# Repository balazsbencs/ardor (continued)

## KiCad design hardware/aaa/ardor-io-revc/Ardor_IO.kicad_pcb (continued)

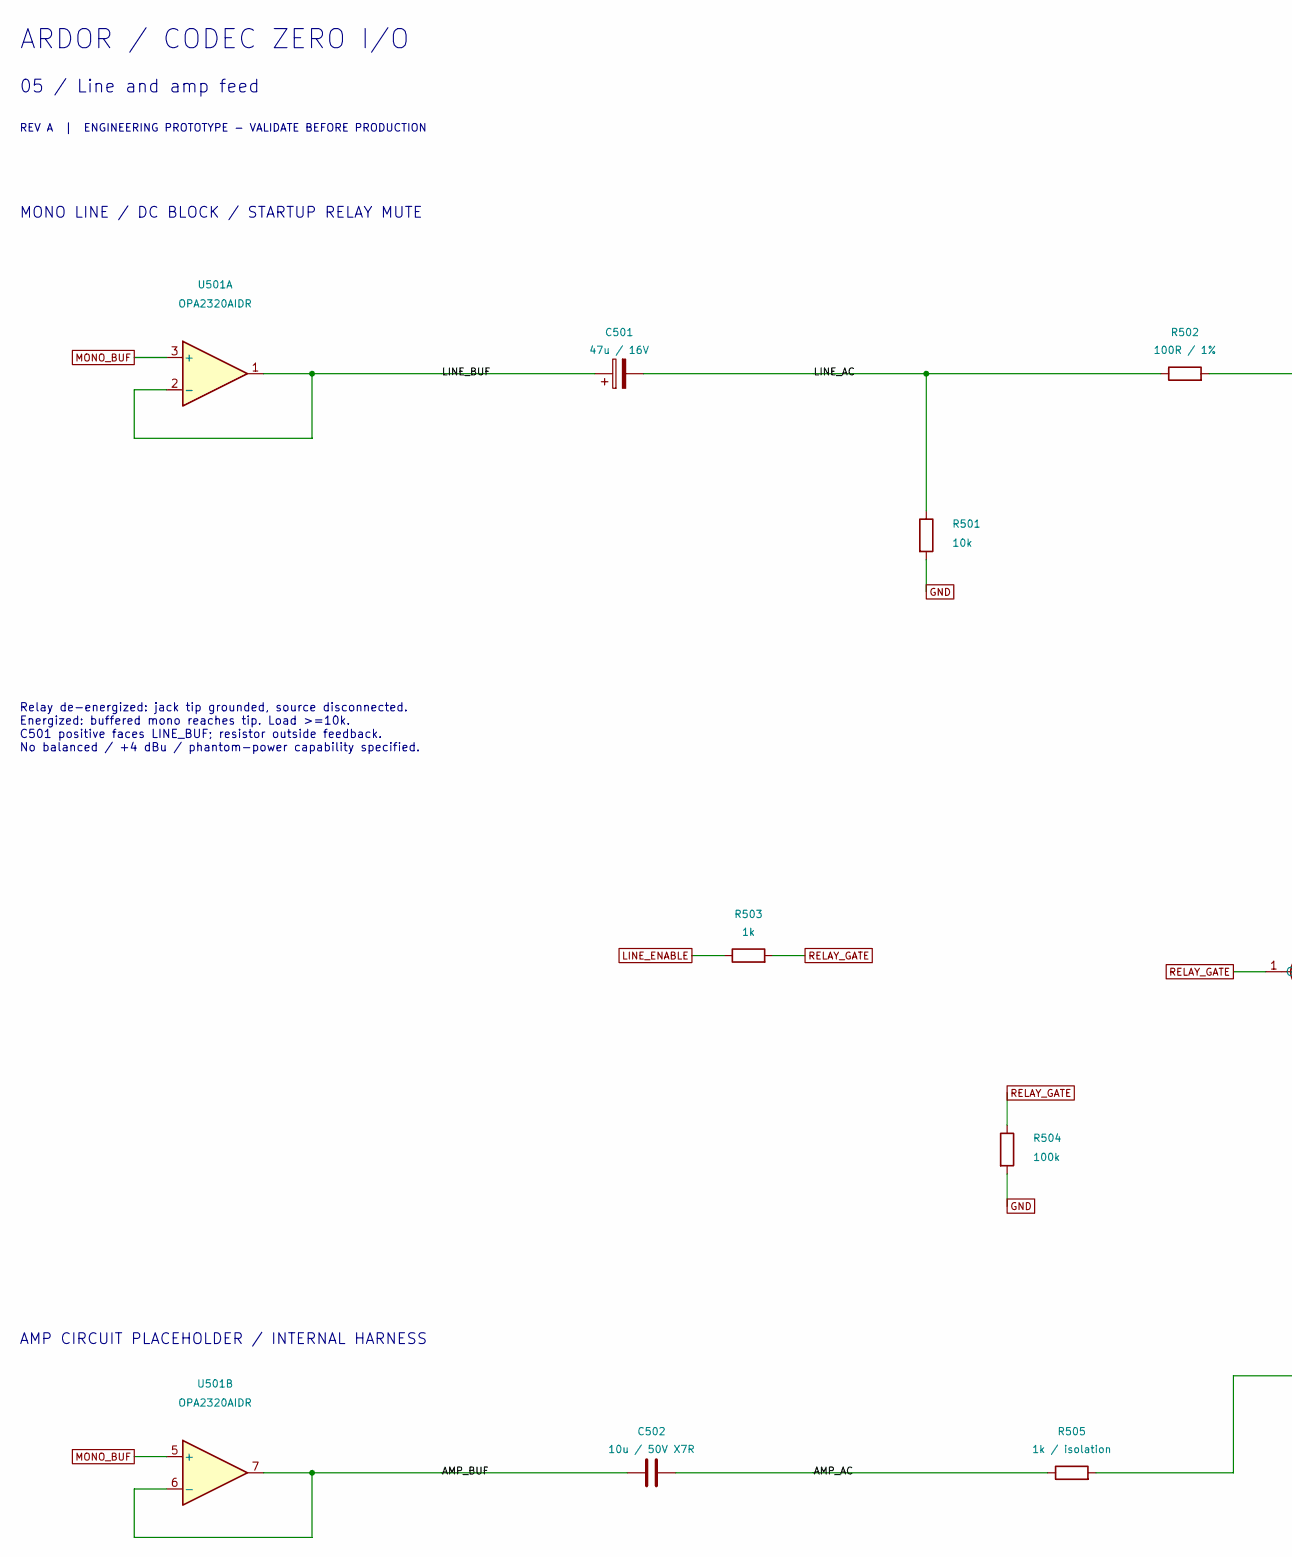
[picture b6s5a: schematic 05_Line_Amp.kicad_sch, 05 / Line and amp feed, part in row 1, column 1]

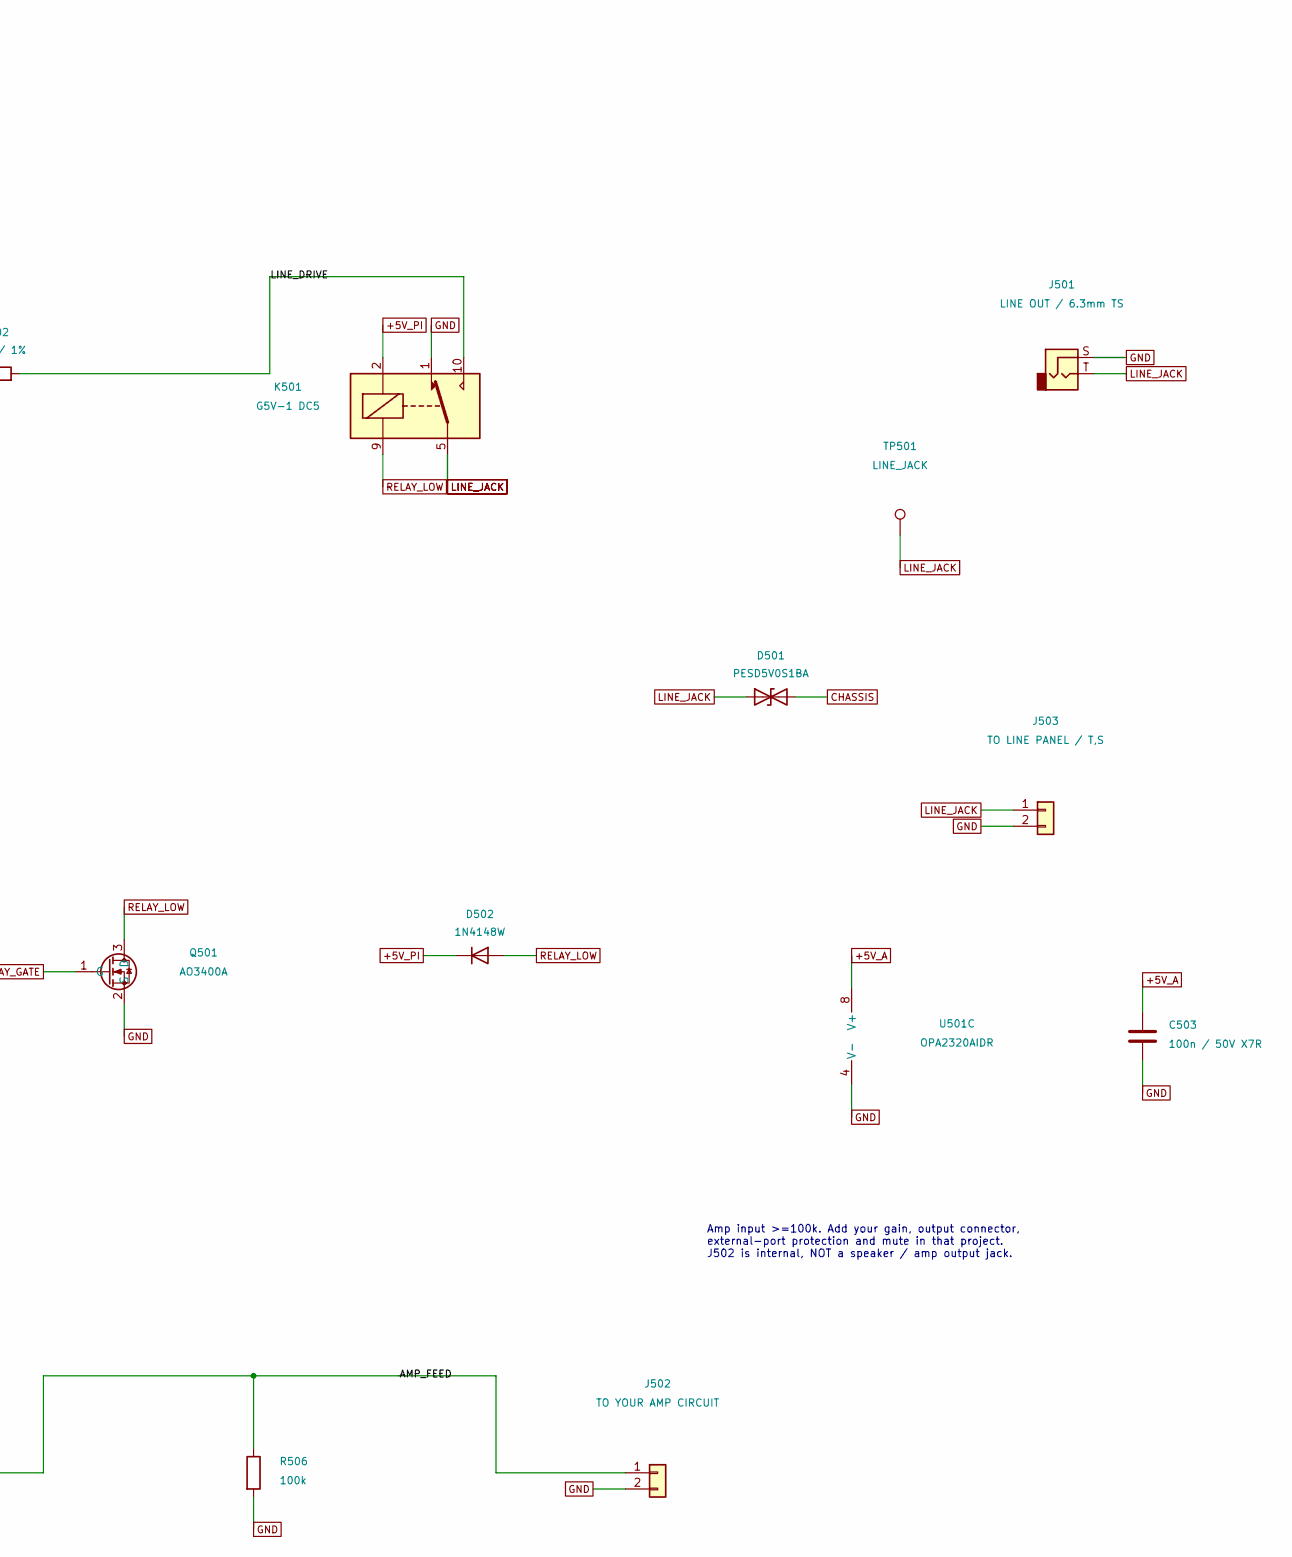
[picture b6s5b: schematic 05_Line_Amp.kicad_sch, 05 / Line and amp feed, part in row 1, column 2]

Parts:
C501: 47u / 16V; CP_Elec_Panasonic_FK_D6.3_H5.8; MPN Panasonic EEEFK1C470P; JLCPCB Part # C336261
C502: 10u / 50V X7R; C_1206_3216Metric; MPN Samsung CL31B106KBHNNNE; JLCPCB Part # C89632
C503: 100n / 50V X7R; C_0603_1608Metric; MPN YAGEO CC0603KRX7R9BB104; JLCPCB Part # C14663
D501: PESD5V0S1BA; D_SOD-323; MPN Nexperia PESD5V0S1BA,115; JLCPCB Part # C19224
D502: 1N4148W; D_SOD-123; MPN ST(Semtech) 1N4148W; JLCPCB Part # C81598
J501: LINE OUT / 6.3mm TS
J502: TO YOUR AMP CIRCUIT; PinHeader_1x02_P2.54mm_Vertical
J503: TO LINE PANEL / T,S; PinHeader_1x02_P2.54mm_Vertical
K501: G5V-1 DC5; Relay_SPDT_Omron_G5V-1; MPN Omron G5V-1 DC5
Q501: AO3400A; SOT-23; MPN Alpha & Omega AO3400A; JLCPCB Part # C20917
R501: 10k; R_0603_1608Metric; MPN UNI-ROYAL 0603WAF1002T5E; JLCPCB Part # C25804
R502: 100R / 1%; R_0603_1608Metric; MPN UNI-ROYAL 0603WAF1000T5E; JLCPCB Part # C22775
R503: 1k; R_0603_1608Metric; MPN UNI-ROYAL 0603WAF1001T5E; JLCPCB Part # C21190
R504, R506: 100k; R_0603_1608Metric; MPN UNI-ROYAL 0603WAF1003T5E; JLCPCB Part # C25803
R505: 1k / isolation; R_0603_1608Metric; MPN UNI-ROYAL 0603WAF1001T5E; JLCPCB Part # C21190
TP501: LINE_JACK; TestPoint_Pad_D1.5mm
U501: OPA2320AIDR; SOIC-8_3.9x4.9mm_P1.27mm; MPN TI OPA2320AIDR; JLCPCB Part # C2863402

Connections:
+5V_PI: D502.1 (K), K501.2; also elsewhere on the board
/05 / Line and amp feed/AMP_AC: C502.2, R505.1
/05 / Line and amp feed/AMP_FEED: J502.1, R505.2, R506.1
/05 / Line and amp feed/LINE_AC: C501.2, R501.1, R502.1
/05 / Line and amp feed/LINE_DRIVE: K501.10, R502.2
CHASSIS: D501.2 (A2); also elsewhere on the board
GND: C503.2, J501.S, J502.2, J503.2, K501.1, Q501.2 (S), R501.2, R504.2, R506.2, U501.4 (V-); also elsewhere on the board
LINE_ENABLE: R503.1; also elsewhere on the board
LINE_JACK: D501.1 (A1), J501.T, J503.1, K501.5, K501.6, TP501.1
unnamed: C503.1, U501.8 (V+)
unnamed: U501.3 (+), U501.5 (+)
RELAY_GATE: Q501.1 (G), R503.2, R504.1
RELAY_LOW: D502.2 (A), K501.9, Q501.3 (D)

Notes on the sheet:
ARDOR / CODEC ZERO I/O
05 / Line and amp feed
REV A | ENGINEERING PROTOTYPE - VALIDATE BEFORE PRODUCTION
MONO LINE / DC BLOCK / STARTUP RELAY MUTE
Relay de-energized: jack tip grounded, source disconnected. Energized: buffered mono reaches tip. Load >=10k. C501 positive faces LINE_BUF; resistor outside feedback. No balanced / +4 dBu / phantom-power capability specified.
AMP CIRCUIT PLACEHOLDER / INTERNAL HARNESS
Amp input >=100k. Add your gain, output connector, external-port protection and mute in that project. J502 is internal, NOT a speaker / amp output jack.

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
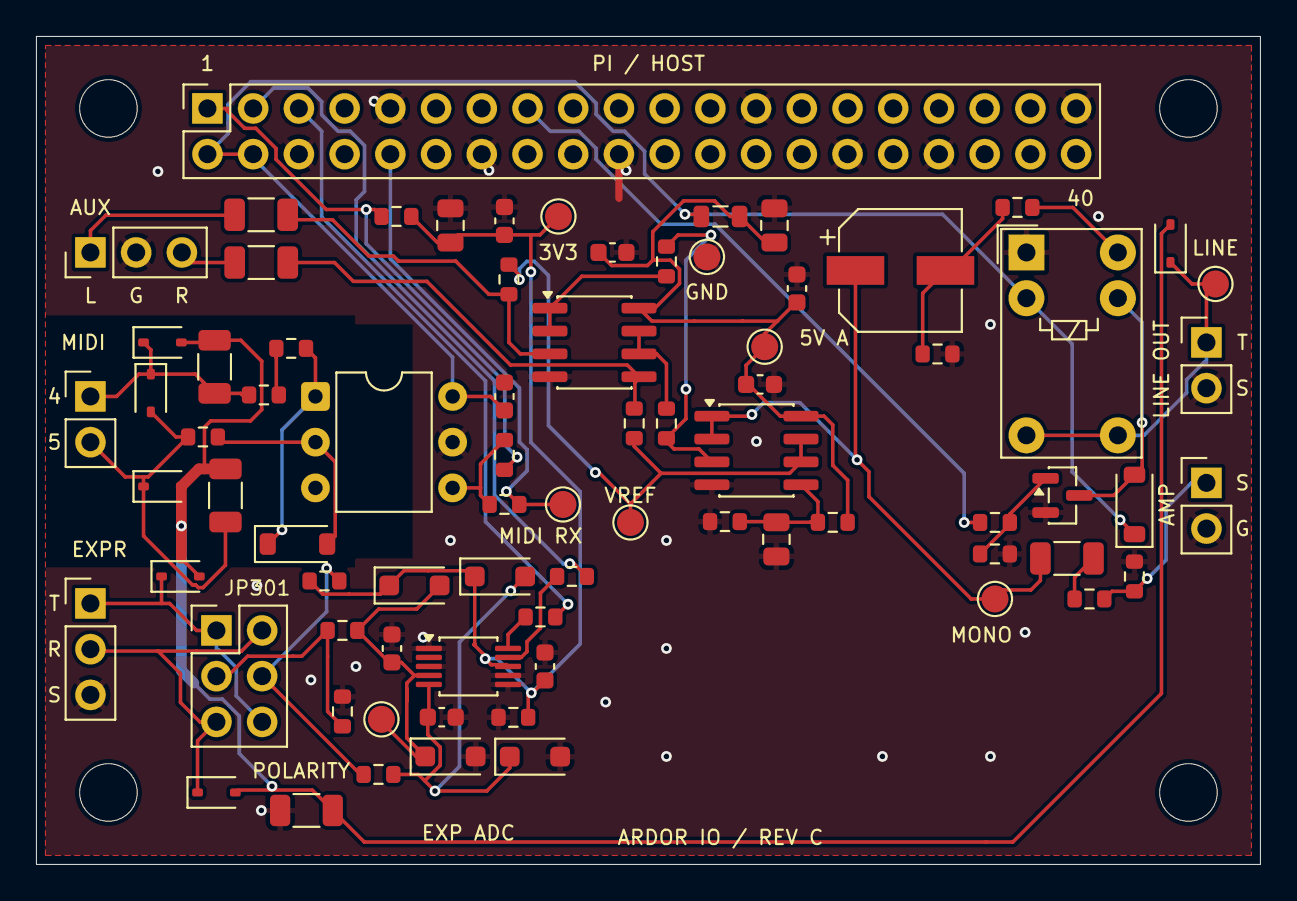
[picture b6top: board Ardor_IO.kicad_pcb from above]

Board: 2 copper layers, 68.0 x 46.0 mm, 81 parts (0 on the bottom side), 41 nets.

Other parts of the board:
H1, H2, H3, H4: M3 / PROVISIONAL; MountingHole_3.2mm_M3

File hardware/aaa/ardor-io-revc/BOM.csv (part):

Reference,Value,MPN,Footprint,Datasheet,Assembly,Sheet,JLCPCB Part #
J101,PI 40-PIN HEADER,Samtec SSQ-120-03-G-D (verify stack height),Connector_PinSocket_2.54mm:PinSocket_2x20_P2.54mm_Vertical,,PCB,1,
J102,CODEC AUX L / GND / R,,Connector_PinHeader_2.54mm:PinHeader_1x03_P2.54mm_Vertical,,PCB,1,
FB101,600R @100MHz,Murata BLM21PG601SN1D,Inductor_SMD:L_0805_2012Metric,https://www.murata.com/products/productdata/8796738977822/EN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,PCB,1,C41556732
C101,22u / 25V X5R,Samsung Electro-Mechanics CL21A226MAQNNNE,Capacitor_SMD:C_0805_2012Metric,https://www.lcsc.com/datasheet/lcsc_datasheet_2304140030_Sam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,PCB,1,C45783
C102,100n / 50V X7R,YAGEO CC0603KRX7R9BB104,Capacitor_SMD:C_0603_1608Metric,https://www.lcsc.com/datasheet/lcsc_datasheet_2211101700_YAG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,PCB,1,C14663
FB102,120R @100MHz,Murata Electronics BLM18PG121SN1D,Resistor_SMD:R_0603_1608Metric,https://www.lcsc.com/datasheet/lcsc_datasheet_2304140030_Mur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,PCB,1,C14709
C103,10u / 25V X5R,Samsung Electro-Mechanics CL21A106KAYNNNE,Capacitor_SMD:C_0805_2012Metric,https://www.lcsc.com/datasheet/lcsc_datasheet_2304140030_Sam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,PCB,1,C15850
C104,100n / 50V X7R,YAGEO CC0603KRX7R9BB104,Capacitor_SMD:C_0603_1608Metric,https://www.lcsc.com/datasheet/lcsc_datasheet_2211101700_YAG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,PCB,1,C14663
R101,0R / chassis bond,UNI-ROYAL 1206W4F0000T5E,Resistor_SMD:R_1206_3216Metric,https://www.lcsc.com/datasheet/lcsc_datasheet_2206010200_UNI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,PCB,1,C17888
J201,MIDI IN - PANEL DIN,,,,Panel / wired,2,
FB201,120R @100MHz,Murata Electronics BLM18PG121SN1D,Resistor_SMD:R_0603_1608Metric,https://www.lcsc.com/datasheet/lcsc_datasheet_2304140030_Mur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,PCB,2,C14709
R201,220R / 1%,UNI-ROYAL 0603WAF2200T5E,Resistor_SMD:R_0603_1608Metric,https://www.lcsc.com/datasheet/lcsc_datasheet_2206010130_UNI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,PCB,2,C22962
FB202,120R @100MHz,Murata Electronics BLM18PG121SN1D,Resistor_SMD:R_0603_1608Metric,https://www.lcsc.com/datasheet/lcsc_datasheet_2304140030_Mur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,PCB,2,C14709
D201,1N4148W,ST(Semtech) 1N4148W,Diode_SMD:D_SOD-123,https://www.lcsc.com/datasheet/lcsc_datasheet_1811061725_ST-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,PCB,2,C81598
U201,H11L1M,onsemi H11L1M,Package_DIP:DIP-6_W7.62mm,https://www.onsemi.com/pdf/datasheet/h11l3m-d.pdf,PCB,2,
C201,100n / 50V X7R,YAGEO CC0603KRX7R9BB104,Capacitor_SMD:C_0603_1608Metric,https://www.lcsc.com/datasheet/lcsc_datasheet_2211101700_YAG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,PCB,2,C14663
R202,1k / 1%,UNI-ROYAL 0603WAF1001T5E,Resistor_SMD:R_0603_1608Metric,https://www.lcsc.com/datasheet/lcsc_datasheet_2206010130_UNI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,PCB,2,C21190
R203,100R,UNI-ROYAL 0603WAF1000T5E,Resistor_SMD:R_0603_1608Metric,https://www.lcsc.com/datasheet/lcsc_datasheet_2411221126_UNI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,PCB,2,C22775
D202,PESD5V0S1BA,"Nexperia PESD5V0S1BA,115",Diode_SMD:D_SOD-323,https://assets.nexperia.com/documents/data-sheet/PESD5V0S1BA.pdf,PCB,2,C19224
C202,100p / 1kV C0G,CCTC TCC1206COG101J102DT,Capacitor_SMD:C_1206_3216Metric,https://wmsc.lcsc.com/wmsc/upload/file/pdf/v2/lcsc/230414003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,PCB,2,C367316
C203,100p / 1kV C0G,CCTC TCC1206COG101J102DT,Capacitor_SMD:C_1206_3216Metric,https://wmsc.lcsc.com/wmsc/upload/file/pdf/v2/lcsc/230414003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,PCB,2,C367316
D203,PESD24VL1BA,"Nexperia PESD24VL1BA,115",Diode_SMD:D_SOD-323,https://assets.nexperia.com/documents/data-sheet/PESD24VL1BA.pdf,PCB,2,C69324
D204,PESD24VL1BA,"Nexperia PESD24VL1BA,115",Diode_SMD:D_SOD-323,https://assets.nexperia.com/documents/data-sheet/PESD24VL1BA.pdf,PCB,2,C69324
J301,EXPRESSION / 6.3mm TRS,,,,Panel / wired,3,
JP301,POLARITY / 2 SHUNTS,,Connector_PinHeader_2.54mm:PinHeader_2x03_P2.54mm_Vertical,,PCB,3,
R301,1k / 1%,UNI-ROYAL 0603WAF1001T5E,Resistor_SMD:R_0603_1608Metric,https://www.lcsc.com/datasheet/lcsc_datasheet_2206010130_UNI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,PCB,3,C21190
R302,10k / 1%,UNI-ROYAL 0603WAF1002T5E,Resistor_SMD:R_0603_1608Metric,https://www.lcsc.com/datasheet/lcsc_datasheet_2206010045_UNI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,PCB,3,C25804
R303,1M,UNI-ROYAL 0603WAF1004T5E,Resistor_SMD:R_0603_1608Metric,https://www.lcsc.com/datasheet/lcsc_datasheet_2206010130_UNI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,PCB,3,C22935
C301,100n / 50V X7R,YAGEO CC0603KRX7R9BB104,Capacitor_SMD:C_0603_1608Metric,https://www.lcsc.com/datasheet/lcsc_datasheet_2211101700_YAG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,PCB,3,C14663
D303,BAT54H,"Nexperia BAT54H,115",Diode_SMD:D_SOD-123F,https://www.lcsc.com/datasheet/lcsc_datasheet_2407241029_Nex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,PCB,3,C426769
D304,BAT54H,"Nexperia BAT54H,115",Diode_SMD:D_SOD-123F,https://www.lcsc.com/datasheet/lcsc_datasheet_2407241029_Nex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,PCB,3,C426769
D301,PESD5V0S1BA,"Nexperia PESD5V0S1BA,115",Diode_SMD:D_SOD-323,https://assets.nexperia.com/documents/data-sheet/PESD5V0S1BA.pdf,PCB,3,C19224
D302,PESD5V0S1BA,"Nexperia PESD5V0S1BA,115",Diode_SMD:D_SOD-323,https://assets.nexperia.com/documents/data-sheet/PESD5V0S1BA.pdf,PCB,3,C19224
U301,ADS1115IDGS,TI ADS1115IDGSR,Package_SO:VSSOP-10_3x3mm_P0.5mm,https://www.ti.com/lit/ds/symlink/ads1115.pdf,PCB,3,C37593
R304,10k / 1%,UNI-ROYAL 0603WAF1002T5E,Resistor_SMD:R_0603_1608Metric,https://www.lcsc.com/datasheet/lcsc_datasheet_2206010045_UNI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,PCB,3,C25804
C302,100n / 50V X7R,YAGEO CC0603KRX7R9BB104,Capacitor_SMD:C_0603_1608Metric,https://www.lcsc.com/datasheet/lcsc_datasheet_2211101700_YAG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,PCB,3,C14663
C303,100n / 50V X7R,YAGEO CC0603KRX7R9BB104,Capacitor_SMD:C_0603_1608Metric,https://www.lcsc.com/datasheet/lcsc_datasheet_2211101700_YAG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,PCB,3,C14663
R305,33R,UNI-ROYAL 0603WAF330JT5E,Resistor_SMD:R_0603_1608Metric,https://www.lcsc.com/datasheet/lcsc_datasheet_2206010116_UNI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,PCB,3,C23140
R306,33R,UNI-ROYAL 0603WAF330JT5E,Resistor_SMD:R_0603_1608Metric,https://www.lcsc.com/datasheet/lcsc_datasheet_2206010116_UNI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,PCB,3,C23140
R307,2.2k / rail bleed,UNI-ROYAL 0603WAF2201T5E,Resistor_SMD:R_0603_1608Metric,https://www.lcsc.com/datasheet/lcsc_datasheet_2206010230_UNI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,PCB,3,C4190
D305,BAT54H,"Nexperia BAT54H,115",Diode_SMD:D_SOD-123F,https://www.lcsc.com/datasheet/lcsc_datasheet_2407241029_Nex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,PCB,3,C426769
D306,BAT54H,"Nexperia BAT54H,115",Diode_SMD:D_SOD-123F,https://www.lcsc.com/datasheet/lcsc_datasheet_2407241029_Nex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,PCB,3,C426769
C401,10u / 50V X5R,Samsung Electro-Mechanics CL31A106KBHNNNE,Capacitor_SMD:C_1206_3216Metric,https://www.lcsc.com/datasheet/lcsc_datasheet_2304140030_Sam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,PCB,4,C13585
R401,100k / 1%,UNI-ROYAL 0603WAF1003T5E,Resistor_SMD:R_0603_1608Metric,https://www.lcsc.com/datasheet/lcsc_datasheet_2206010045_UNI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,PCB,4,C25803
U401,TLV9002IDR,Texas Instruments TLV9002IDR,Package_SO:SOIC-8_3.9x4.9mm_P1.27mm,https://www.lcsc.com/datasheet/lcsc_datasheet_2304140030_Tex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,PCB,4,C398360
R403,10k / 1%,UNI-ROYAL 0603WAF1002T5E,Resistor_SMD:R_0603_1608Metric,https://www.lcsc.com/datasheet/lcsc_datasheet_2206010045_UNI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,PCB,4,C25804
C402,10u / 50V X5R,Samsung Electro-Mechanics CL31A106KBHNNNE,Capacitor_SMD:C_1206_3216Metric,https://www.lcsc.com/datasheet/lcsc_datasheet_2304140030_Sam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,PCB,4,C13585
R402,100k / 1%,UNI-ROYAL 0603WAF1003T5E,Resistor_SMD:R_0603_1608Metric,https://www.lcsc.com/datasheet/lcsc_datasheet_2206010045_UNI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,PCB,4,C25803
R404,10k / 1%,UNI-ROYAL 0603WAF1002T5E,Resistor_SMD:R_0603_1608Metric,https://www.lcsc.com/datasheet/lcsc_datasheet_2206010045_UNI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,PCB,4,C25804
U402,TLV9002IDR,Texas Instruments TLV9002IDR,Package_SO:SOIC-8_3.9x4.9mm_P1.27mm,https://www.lcsc.com/datasheet/lcsc_datasheet_2304140030_Tex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,PCB,4,C398360
R405,10k / 1%,UNI-ROYAL 0603WAF1002T5E,Resistor_SMD:R_0603_1608Metric,https://www.lcsc.com/datasheet/lcsc_datasheet_2206010045_UNI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,PCB,4,C25804
R406,10k / 1%,UNI-ROYAL 0603WAF1002T5E,Resistor_SMD:R_0603_1608Metric,https://www.lcsc.com/datasheet/lcsc_datasheet_2206010045_UNI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,PCB,4,C25804
C403,10u / 25V X5R,Samsung Electro-Mechanics CL21A106KAYNNNE,Capacitor_SMD:C_0805_2012Metric,https://www.lcsc.com/datasheet/lcsc_datasheet_2304140030_Sam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,PCB,4,C15850
C404,100n / 50V X7R,YAGEO CC0603KRX7R9BB104,Capacitor_SMD:C_0603_1608Metric,https://www.lcsc.com/datasheet/lcsc_datasheet_2211101700_YAG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,PCB,4,C14663
C405,100n / 50V X7R,YAGEO CC0603KRX7R9BB104,Capacitor_SMD:C_0603_1608Metric,https://www.lcsc.com/datasheet/lcsc_datasheet_2211101700_YAG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,PCB,4,C14663
C501,47u / 16V,Panasonic EEEFK1C470P,Ardor_Capacitor:CP_Elec_Panasonic_FK_D6.3_H5.8,https://industrial.panasonic.com/cdbs/www-data/pdf/RDE0000/A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,PCB,5,C336261
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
